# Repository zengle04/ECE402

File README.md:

# ECE402 Final Project
This is a senior design project for The University of Tennessee, Knoxville
It is a ESP32 based Bluetooth Headphone DAC/AMP

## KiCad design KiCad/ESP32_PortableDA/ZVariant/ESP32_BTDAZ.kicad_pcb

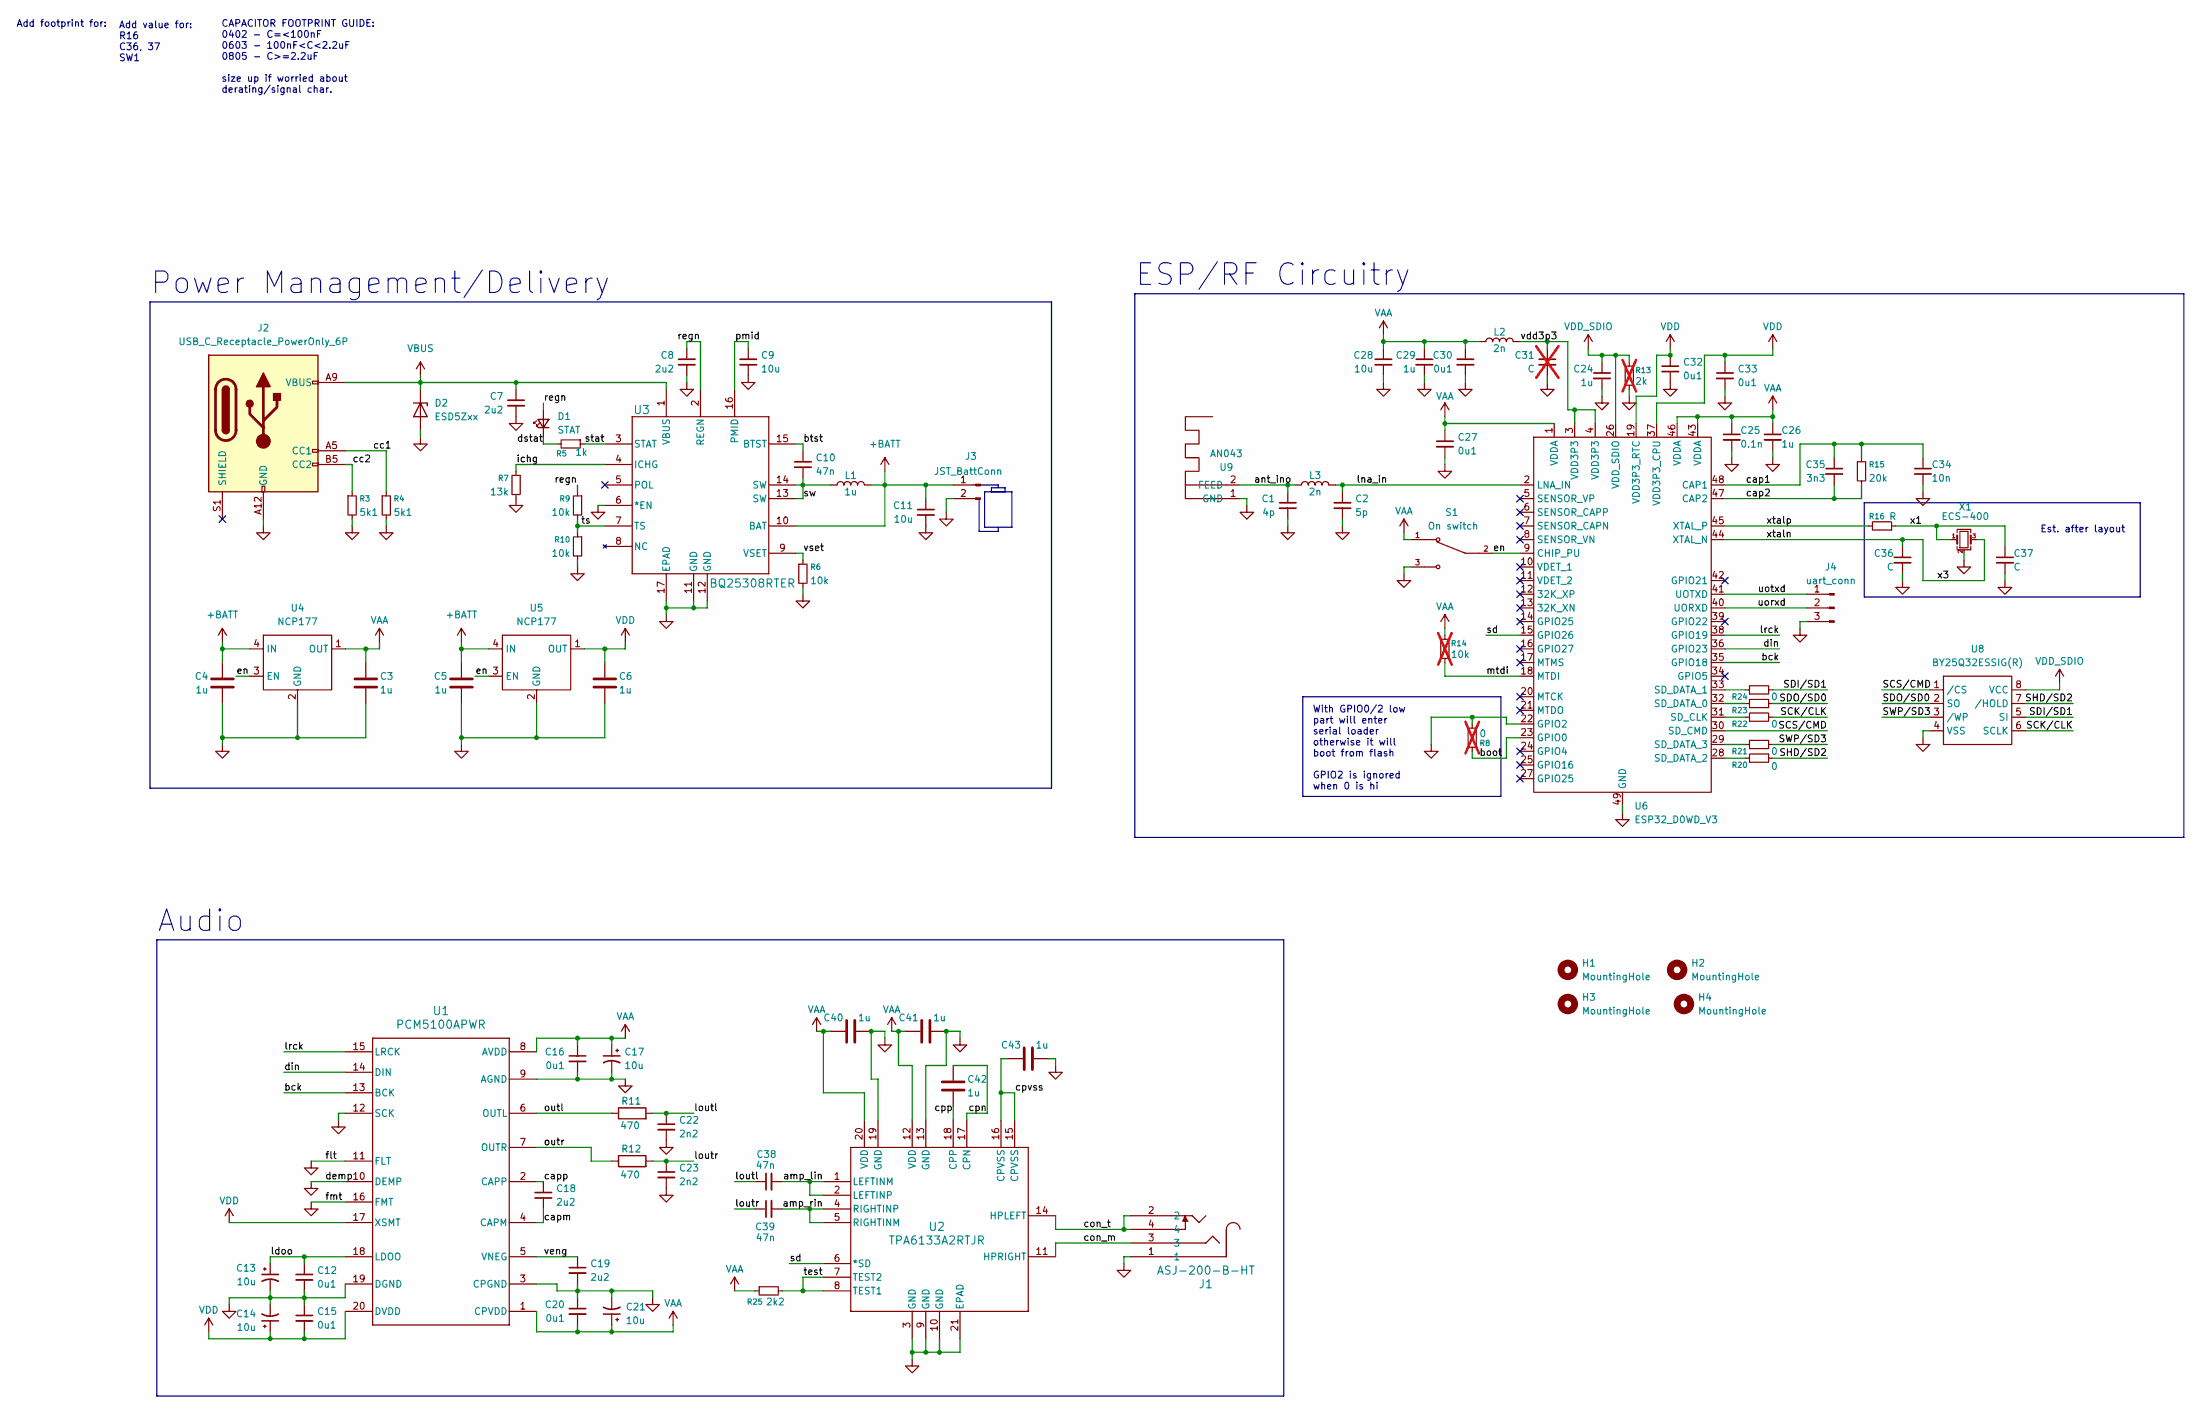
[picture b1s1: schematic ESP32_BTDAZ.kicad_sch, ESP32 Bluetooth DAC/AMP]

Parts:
C1: 4p; C_0402_1005Metric
C2: 5p; C_0402_1005Metric
C3, C4, C5, C6, C24, C26, C29, C40, C41, C42, C43: 1u; C_0603_1608Metric
C7, C8, C19: 2u2; C_0805_2012Metric
C9, C11, C13, C14, C17, C21, C28: 10u; C_0805_2012Metric
C10, C38, C39: 47n; C_0402_1005Metric
C12, C15, C16, C20: 0u1; C_0603_1608Metric
C18: 2u2; C_0402_1005Metric
C22, C23: 2n2; C_0805_2012Metric
C25: 0.1n; C_0402_1005Metric
C27, C30, C32, C33: 0u1; C_0402_1005Metric
C31: C; C_0603_1608Metric; not fitted
C34: 10n; C_0402_1005Metric
C35: 3n3; C_0402_1005Metric
C36, C37: C; C_0402_1005Metric
D1: STAT; LED_0603_1608Metric
D2: ESD5Zxx; D_SOD-523
H1, H2, H3, H4: MountingHole; MountingHole_2.2mm_M2_DIN965_Pad_TopBottom
J1: ASJ-200-B-HT; ASJ-200-B-HT_ADM
J2: USB_C_Receptacle_PowerOnly_6P; USB_C_Receptacle_GCT_USB4125-xx-x_6P_TopMnt_Horizontal
J3: JST_BattConn; JST_PH_S2B-PH-K_1x02_P2.00mm_Horizontal
J4: uart_conn; PinHeader_1x03_P2.54mm_Vertical
L1: 1u; L_0805_2012Metric
L2, L3: 2n; L_0402_1005Metric
R3, R4: 5k1; R_0402_1005Metric
R5: 1k; R_0402_1005Metric
R6, R9, R10: 10k; R_0402_1005Metric
R7: 13k; R_0402_1005Metric
R8: 0; R_0402_1005Metric; not fitted
R11, R12: 470; R_0603_1608Metric
R13: 2k; R_0402_1005Metric; not fitted
R14: 10k; R_0402_1005Metric; not fitted
R15: 20k; R_0402_1005Metric
R16: R; R_0402_1005Metric
R20, R21, R22, R23, R24: 0; R_0402_1005Metric
R25: 2k2; R_0402_1005Metric
S1: On switch; SW_SLW-129956-4A-RA-N-D; PARTREV 1.01
U1: PCM5100APWR; TSSOP-20_4.4x6.5mm_P0.65mm; Part No. PCM5100APWR
U2: TPA6133A2RTJR; RTJ20_2P7X2P7_TEX
U3: BQ25308RTER; WQFN16_RTE_TEX
U4, U5: NCP177; OnSemi_XDFN4-1EP_1.0x1.0mm_EP0.52x0.52mm; Part No NCP177BMX330TCG
U6: ESP32_D0WD_V3; QFN-48-1EP_5x5mm_P0.35mm_EP3.7x3.7mm_ThermalVias; Part No ESP32-D0WD-V3
U8: BY25Q32ESSIG(R); SOP-8_3.76x4.96mm_P1.27mm; Part No BY25Q32ESSIG(R)
U9: AN043; AN043_2.4GHz_PCB_Antenna
X1: ECS-400; Crystal_SMD_2016-4Pin_2.0x1.6mm

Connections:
+BATT: C4.1, C5.1, C11.1, J3.1, L1.2, U3.10 (BAT), U4.4 (IN), U5.4 (IN)
/SCK/CLK: R22.2, U8.6 (SCLK)
/SCS/CMD: U6.30 (SD_CMD), U8.1 (/CS)
/SDI/SD1: R24.2, U8.5 (SI)
/SDO/SD0: R23.2, U8.2 (SO)
/SHD/SD2: R20.2, U8.7 (/HOLD)
/SWP/SD3: R21.2, U8.3 (/WP)
/amp_lin: C38.2, U2.1 (LEFTINM), U2.2 (LEFTINP)
/amp_rin: C39.2, U2.4 (RIGHTINP), U2.5 (RIGHTINM)
/ant_ino: C1.1, L3.1, U9.2 (FEED)
/bck: U1.13 (BCK), U6.35 (GPIO18)
/boot: R8.1, U6.23 (GPIO0)
/btst: C10.1, U3.15 (BTST)
/cap1: C34.1, C35.1, R15.1, U6.48 (CAP1)
/cap2: C35.2, R15.2, U6.47 (CAP2)
/capm: C18.2, U1.4 (CAPM)
/capp: C18.1, U1.2 (CAPP)
/cc1: J2.A5 (CC1), R4.1
/cc2: J2.B5 (CC2), R3.1
/con_m: J1.3, U2.11 (HPRIGHT)
/con_t: J1.2, J1.4, U2.14 (HPLEFT)
/cpn: C42.1, U2.17 (CPN)
/cpp: C42.2, U2.18 (CPP)
/cpvss: C43.1, U2.15 (CPVSS), U2.16 (CPVSS)
/din: U1.14 (DIN), U6.36 (GPIO23)
/dstat: D1.1 (K), R5.2
/en: S1.2, U4.3 (EN), U5.3 (EN), U6.9 (CHIP_PU)
/ichg: R7.1, U3.4 (ICHG)
/ldoo: C12.1, C13.1, U1.18 (LDOO)
/lna_in: C2.1, L3.2, U6.2 (LNA_IN)
/loutl: C22.1, C38.1, R11.2
/loutr: C23.1, C39.1, R12.2
/lrck: U1.15 (LRCK), U6.38 (GPIO19)
/mtdi: R14.2, U6.18 (MTDI)
/outl: R11.1, U1.6 (OUTL)
/outr: R12.1, U1.7 (OUTR)
/pmid: C9.1, U3.16 (PMID)
/regn: C8.1, D1.2 (A), R9.1, U3.2 (REGN)
/sd: U2.6 (*SD), U6.15 (GPIO26)
/stat: R5.1, U3.3 (STAT)
/sw: C10.2, L1.1, U3.13 (SW), U3.14 (SW)
/test: R25.2, U2.7 (TEST2), U2.8 (TEST1)
/ts: R9.2, R10.1, U3.7 (TS)
/uorxd: J4.2, U6.40 (UORXD)
/uotxd: J4.1, U6.41 (UOTXD)
/vdd3p3: C31.1, L2.2, U6.3 (VDD3P3), U6.4 (VDD3P3)
/veng: C19.1, U1.5 (VNEG)
/vset: R6.1, U3.9 (VSET)
/x1: C37.1, R16.1, X1.1
/x3: C36.1, U6.44 (XTAL_N), X1.3
/xtalp: R16.2, U6.45 (XTAL_P)
GND: C1.2, C2.2, C3.2, C4.2, C5.2, C6.2, C7.2, C8.2, C9.2, C11.2, C12.2, C13.2, C14.2, C15.1, C16.2, C17.2, C19.2, C20.1, C21.2, C22.2, C23.2, C24.2, C25.2, C26.2, C27.2, C28.2, C29.2, C30.2, C31.2, C32.2, C33.2, C34.2, C36.2, C37.2, C40.2, C41.2, C43.2, D2.2 (A), J1.1, J2.A12 (GND), J2.B12 (GND), J3.2, J4.3, R3.2, R4.2, R6.2, R7.2, R8.2, R10.2, R13.2, S1.3, U1.3 (CPGND), U1.9 (AGND), U1.10 (DEMP), U1.11 (FLT), U1.12 (SCK), U1.16 (FMT), U1.19 (DGND), U2.3 (GND), U2.9 (GND), U2.10 (GND), U2.13 (GND), U2.19 (GND), U2.21 (EPAD), U3.6 (*EN), U3.11 (GND), U3.12 (GND), U3.17 (EPAD), U4.2 (GND), U5.2 (GND), U6.22 (GPIO2), U6.49 (GND), U8.4 (VSS), U9.1 (GND), X1.2 (G), X1.4 (G)
unnamed: R22.1, U6.31 (SD_CLK)
unnamed: R23.1, U6.32 (SD_DATA_0)
unnamed: R24.1, U6.33 (SD_DATA_1)
unnamed: R20.1, U6.28 (SD_DATA_2)
unnamed: R21.1, U6.29 (SD_DATA_3)
VAA: C3.1, C16.1, C17.1, C20.2, C21.1, C25.1, C26.1, C27.1, C28.1, C29.1, C30.1, C40.1, C41.1, L2.1, R14.1, R25.1, S1.1, U1.1 (CPVDD), U1.8 (AVDD), U2.12 (VDD), U2.20 (VDD), U4.1 (OUT), U6.1 (VDDA), U6.43 (VDDA), U6.46 (VDDA)
VBUS: C7.1, D2.1 (K), J2.A9 (VBUS), J2.B9 (VBUS), U3.1 (VBUS)
VDD: C6.1, C14.1, C15.2, C32.1, C33.1, U1.17 (XSMT), U1.20 (DVDD), U5.1 (OUT), U6.19 (VDD3P3_RTC), U6.37 (VDD3P3_CPU)
VDD_SDIO: C24.1, R13.1, U6.26 (VDD_SDIO), U8.8 (VCC)

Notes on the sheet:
CAPACITOR FOOTPRINT GUIDE: 0402 - C=<100nF 0603 - 100nF<C<2.2uF 0805 - C>=2.2uF size up if worried about derating/signal char.
Est. after layout
Audio
Add value for: R16 C36, 37 SW1
With GPIO0/2 low part will enter serial loader otherwise it will boot from flash GPIO2 is ignored when 0 is hi
ESP/RF Circuitry
Power Management/Delivery
Add footprint for:

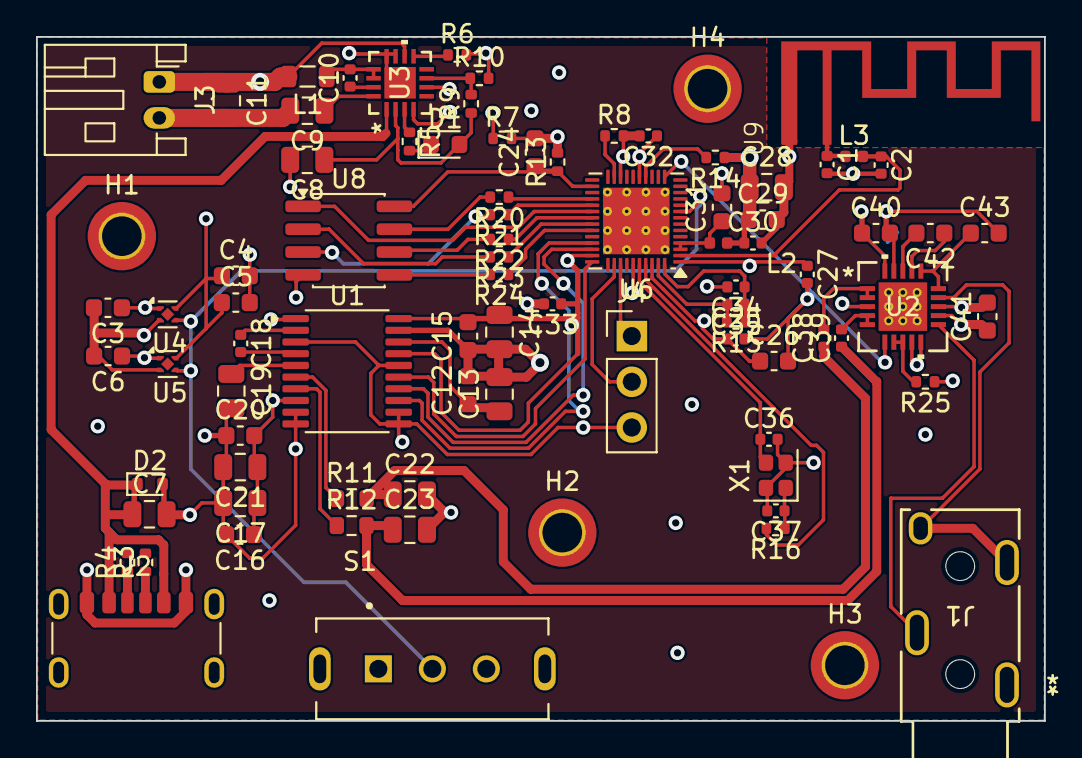
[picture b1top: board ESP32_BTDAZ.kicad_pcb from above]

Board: 4 copper layers, 56.0 x 38.0 mm, 86 parts (0 on the bottom side), 61 nets.

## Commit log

2026-02-18 Added Parts
2026-02-18 Added KiCad Project
2026-02-19 Fixed problems with BC and DAC schematics
2026-02-19 Updated BC and DAC schematics
2026-02-19 Updated BC and DAC footprints
    - Added Mfg and part no
    - Added links to suppliers
    - Changed footprints to default KiCad library that more closely matched data sheet
2026-03-03 Updated Schematics
    Full schematic with net labels and all footprints on board, missing some 3D models
2026-03-03 Added More Parts
    Add switch, audio jack, new LDO, and memory
2026-03-08 Added 3D model for jack
2026-03-08 Added colors to switch
2026-03-08 Updated Footprints - Fixed Antenna
2026-03-08 Updated Schematic
    added mounting holes, finished revision one, and unplaced/routed board (undone)
2026-03-11 Add files via upload
    Layout and Routing detailing, spacing/DRC issues unresolved - discuss during design review
2026-03-16 Zeke's Attempt
